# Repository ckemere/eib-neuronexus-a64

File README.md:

# EIB for Neuronexus A64 probes

- 64 electrodes
- Power ground (GND) and amplifier reference (REF) exposed via 2.54mm header
- Compatible with
  [headstage-64](https://github.com/open-ephys/onix-headstage-64) Rev. 1.3 and 1.3B, [headstage-64s](https://github.com/open-ephys/onix-headstage-64s), and the [low-profile headstage](https://open-ephys.org/acquisition-system/low-profile-spi-headstage-64ch). 

# Notes about this fork:
This repository is a fork of https://github.com/open-ephys/eib-neuronexus-a64. 
I've replaced the through-hole connector from
that design with a SMD connector (i.e., FOLC-110-02-S-Q-P). While this makes
alignment of the two connectors much more challenging, it allows for
fabrication with a standard 2-layer PCB process with 6 mil trace/space.

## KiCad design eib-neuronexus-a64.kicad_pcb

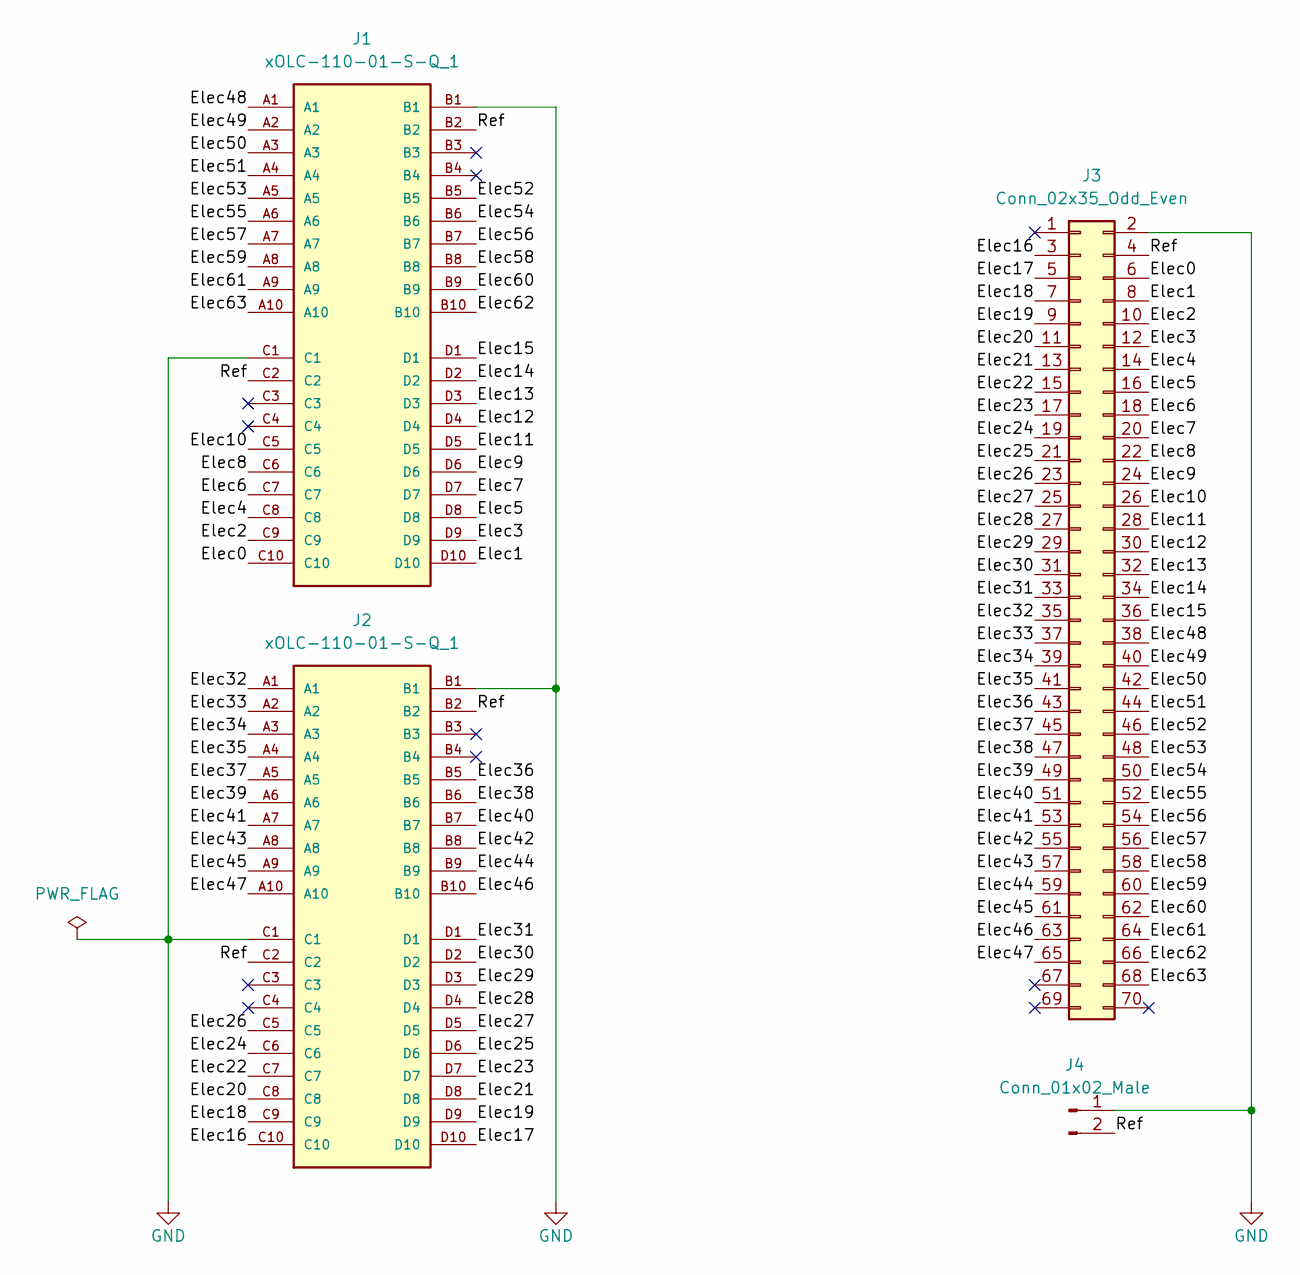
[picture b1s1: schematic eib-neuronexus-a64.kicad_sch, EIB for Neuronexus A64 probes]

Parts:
J1, J2: xOLC-110-01-S-Q_1; SAMTEC_FOLC-110-02-S-Q-LC
J3: Conn_02x35_Odd_Even; HIROSE_DF40C(2.0)-70DS-0.4V(51)
J4: Conn_01x02_Male; PinHeader_1x02_P2.54mm_Horizontal

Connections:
/Elec0: J1.C10, J3.6
/Elec1: J1.D10, J3.8
/Elec2: J1.C9, J3.10
/Elec3: J1.D9, J3.12
/Elec4: J1.C8, J3.14
/Elec5: J1.D8, J3.16
/Elec6: J1.C7, J3.18
/Elec7: J1.D7, J3.20
/Elec8: J1.C6, J3.22
/Elec9: J1.D6, J3.24
/Elec10: J1.C5, J3.26
/Elec11: J1.D5, J3.28
/Elec12: J1.D4, J3.30
/Elec13: J1.D3, J3.32
/Elec14: J1.D2, J3.34
/Elec15: J1.D1, J3.36
/Elec16: J2.C10, J3.3
/Elec17: J2.D10, J3.5
/Elec18: J2.C9, J3.7
/Elec19: J2.D9, J3.9
/Elec20: J2.C8, J3.11
/Elec21: J2.D8, J3.13
/Elec22: J2.C7, J3.15
/Elec23: J2.D7, J3.17
/Elec24: J2.C6, J3.19
/Elec25: J2.D6, J3.21
/Elec26: J2.C5, J3.23
/Elec27: J2.D5, J3.25
/Elec28: J2.D4, J3.27
/Elec29: J2.D3, J3.29
/Elec30: J2.D2, J3.31
/Elec31: J2.D1, J3.33
/Elec32: J2.A1, J3.35
/Elec33: J2.A2, J3.37
/Elec34: J2.A3, J3.39
/Elec35: J2.A4, J3.41
/Elec36: J2.B5, J3.43
/Elec37: J2.A5, J3.45
/Elec38: J2.B6, J3.47
/Elec39: J2.A6, J3.49
/Elec40: J2.B7, J3.51
/Elec41: J2.A7, J3.53
/Elec42: J2.B8, J3.55
/Elec43: J2.A8, J3.57
/Elec44: J2.B9, J3.59
/Elec45: J2.A9, J3.61
/Elec46: J2.B10, J3.63
/Elec47: J2.A10, J3.65
/Elec48: J1.A1, J3.38
/Elec49: J1.A2, J3.40
/Elec50: J1.A3, J3.42
/Elec51: J1.A4, J3.44
/Elec52: J1.B5, J3.46
/Elec53: J1.A5, J3.48
/Elec54: J1.B6, J3.50
/Elec55: J1.A6, J3.52
/Elec56: J1.B7, J3.54
/Elec57: J1.A7, J3.56
/Elec58: J1.B8, J3.58
/Elec59: J1.A8, J3.60
/Elec60: J1.B9, J3.62
/Elec61: J1.A9, J3.64
/Elec62: J1.B10, J3.66
/Elec63: J1.A10, J3.68
/Ref: J1.B2, J1.C2, J2.B2, J2.C2, J3.4, J4.2
GND: J1.B1, J1.C1, J2.B1, J2.C1, J3.2, J4.1

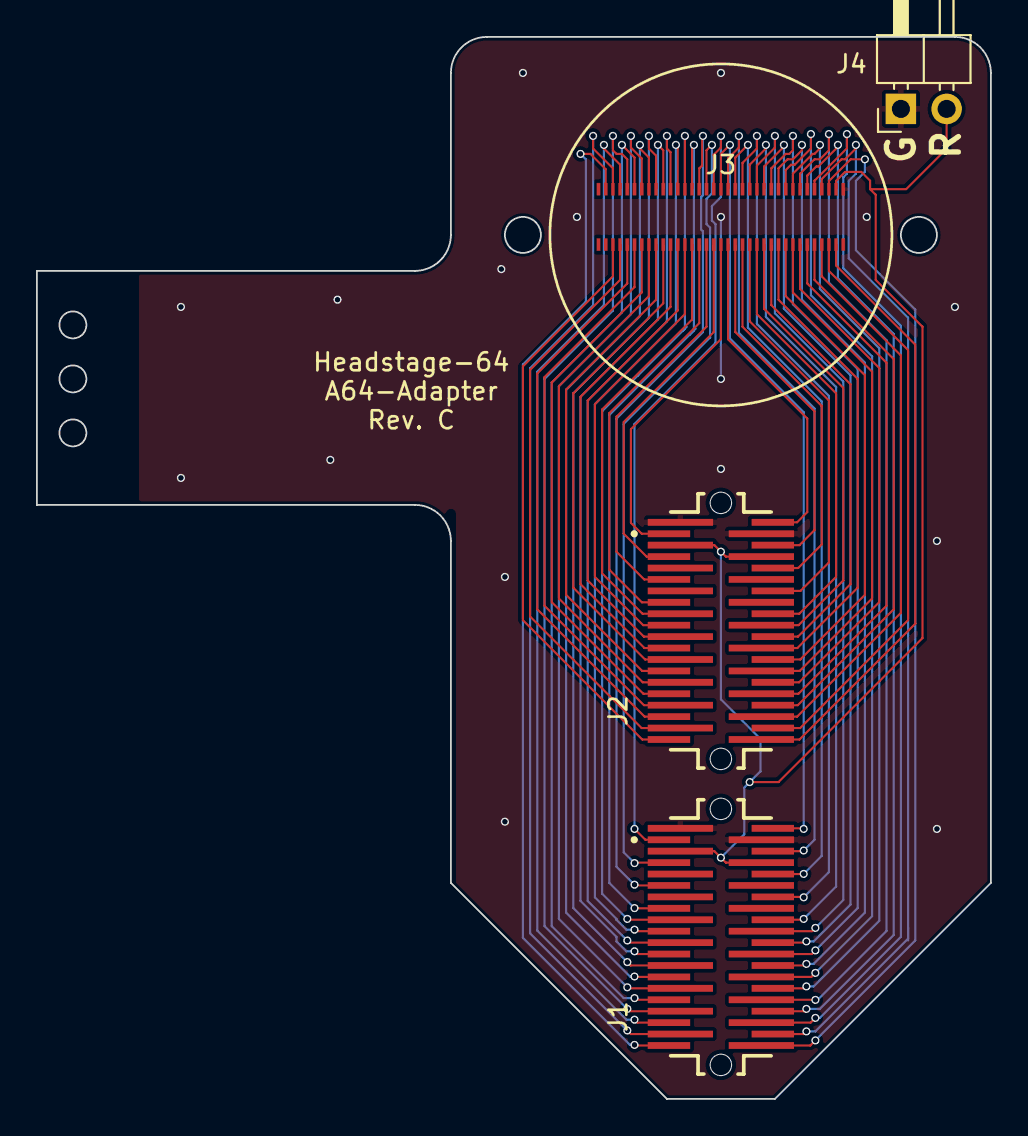
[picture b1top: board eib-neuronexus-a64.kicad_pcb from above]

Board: 2 copper layers, 53.0 x 59.0 mm, 4 parts (0 on the bottom side), 66 nets.

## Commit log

2025-07-23 Updated with alternative SMD package for big 5x8 connector
2025-07-23 Updates for fork
